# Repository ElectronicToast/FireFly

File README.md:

# FireFly

Open source ATmega8 target board with voltage regulation and ICSP, FTDI breakouts.

&nbsp;

## Description

FIREFLY is an open-source ATmega8 (ATmega328) target board that might be likened to a lightweight yet accessible Arduino Uno R3. It is intended to be used for learning AVR C/C++ or AVR Assembly with Atmel Studio. A 16 MHz oscillator and reset circuit is provided for a complete microcontroller system. 5V and 3V3 power are created from DC input. The 28 pins of the ATmega8 DIP package are brought out onto breadboard-compatible headers so that the whole board may be plugged directly into a breadboard and used.

The ATmega8 may be programmed through the onboard ICSP or FTDI headers with an appropriate programmer. The power source for the target may be selected by a jumper shunt; when programming, take care not to power the target through the DC input (VIN) in addition to the programmer.

Designed with KiCad EDA 5.0.1. Gerber and drill files for fabrication may be found in `/gerber`, while documentation in pdf format may be found in `/pdf`. 

## Author
- Ray Sun - Undergraduate, Electrical Engineering, Caltech, Class of 2020

I created this board to help me enhance my knowledge of embedded systems development and working with AVRs.

## Licensing
<br />This work is licensed under a <a rel="license" href="http://creativecommons.org/licenses/by-sa/3.0/">Creative Commons Attribution-ShareAlike 3.0 Unported License</a>.

This design is a derivative of the [Arduino Uno Rev3](https://store.arduino.cc/usa/arduino-uno-rev3) board and is inspired by Adafruit Industries' [DC Boarduino](https://www.adafruit.com/product/72) by Limor Fried. Arduino is a trademark of Arduino AG. This design is not affiliated with Arduino AG.

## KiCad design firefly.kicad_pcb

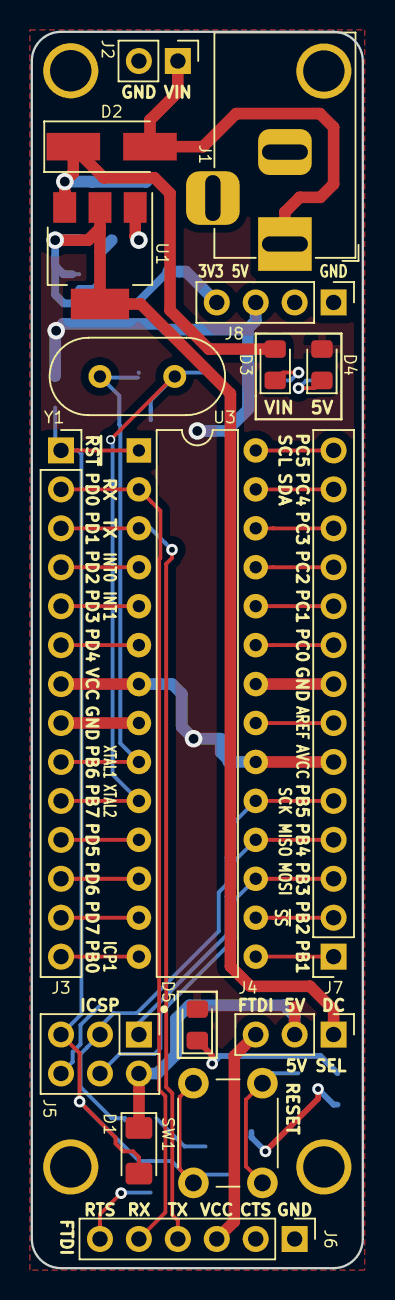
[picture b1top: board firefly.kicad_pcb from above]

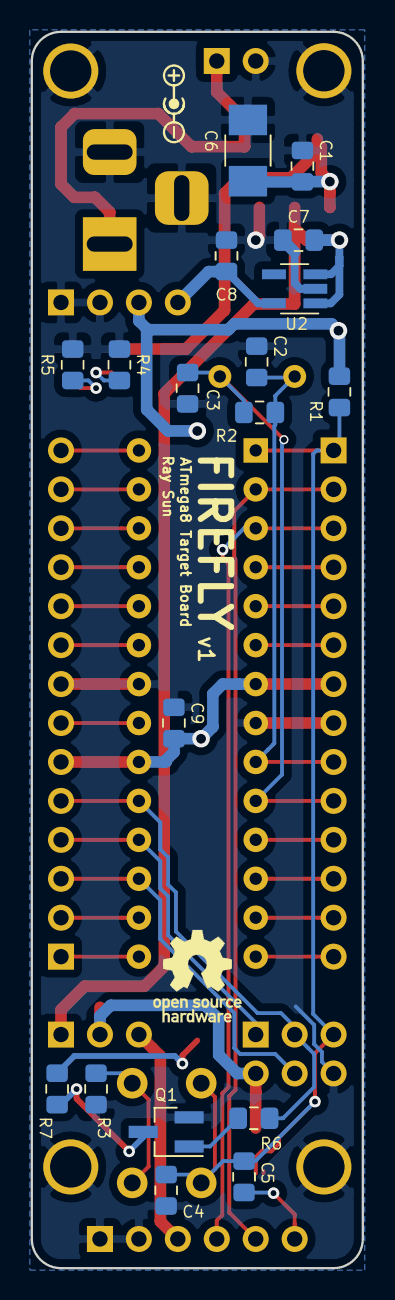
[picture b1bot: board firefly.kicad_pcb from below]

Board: 2 copper layers, 21.6 x 80.6 mm, 35 parts (18 on the bottom side), 38 nets.

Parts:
C1, C7: 10uF; C_0805_2012Metric_Pad1.15x1.40mm_HandSolder
C2, C3: 20pF; C_0805_2012Metric_Pad1.15x1.40mm_HandSolder
C4, C8: 1uF; C_0805_2012Metric_Pad1.15x1.40mm_HandSolder
C5, C9: 0.1uF; C_0805_2012Metric_Pad1.15x1.40mm_HandSolder
C6: 10uF; C_1210_HandSoldering
D1: CD1206-S01575; D_1206_3216Metric_Pad1.42x1.75mm_HandSolder
D2: M7; D_SMA_Handsoldering
D3: LTST-C171KRKT; LED_0805_2012Metric_Pad1.15x1.40mm_HandSolder
D4: LTST-C171KGKT; LED_0805_2012Metric_Pad1.15x1.40mm_HandSolder
D5: LTST-C171TBKT; LED_0805_2012Metric_Pad1.15x1.40mm_HandSolder
J1: Barrel_Jack; BarrelJack_Horizontal
J2: Conn_01x02; PinHeader_1x02_P2.54mm_Vertical
J3, J7: Conn_01x14; PinSocket_1x14_P2.54mm_Vertical
J4: Power_Jumper; PinHeader_1x03_P2.54mm_Vertical
J5: Conn_02x03_Odd_Even; PinHeader_2x03_P2.54mm_Vertical
J6: Conn_01x06; PinHeader_1x06_P2.54mm_Vertical
J8: Conn_01x04; PinHeader_1x04_P2.54mm_Vertical
Q1: NTR5103; SOT-23_Handsoldering
R1: 10K; R_0805_2012Metric_Pad1.15x1.40mm_HandSolder
R2: 1M; R_0805_2012Metric_Pad1.15x1.40mm_HandSolder
R3: 100; R_0805_2012Metric_Pad1.15x1.40mm_HandSolder
R4, R5, R6: 1K; R_0805_2012Metric_Pad1.15x1.40mm_HandSolder
R7: 330; R_0805_2012Metric_Pad1.15x1.40mm_HandSolder
SW1: SW_Push; SW_PUSH_6mm
U1: NCP1117-5.0_SOT223; SOT-223-3_TabPin2
U2: LP2985-3.3; SOT-23-5_HandSoldering
U3: ATmega328P-PU; DIP-28_W7.62mm
Y1: 16 MHz; Crystal_HC49-4H_Vertical

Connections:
+3V3: C8.1, J8.4, U2.5
+5V: C9.1, D1.1, D4.2, D5.2, J3.7, J4.2, J5.2, J7.6, J8.3, R1.1, U3.7, U3.20
/DC_5V: C7.1, J4.1, U1.2, U2.1, U2.3
/MISO: J5.1, J7.4, U3.18
/MOSI: J5.4, J7.3, U3.17
/OSC1: C2.1, J3.9, R2.1, U3.9, Y1.1
/OSC2: C3.1, J3.10, R2.2, U3.10, Y1.2
/P1: C4.1, C5.2, D1.2, J3.1, J5.5, R1.2, SW1.1, U3.1
/P2: J3.2, J6.5, U3.2
/P3: J3.3, J6.4, U3.3
/P4: J3.4, U3.4
/P5: J3.5, U3.5
/P6: J3.6, U3.6
/P11: J3.11, U3.11
/P12: J3.12, U3.12
/P13: J3.13, U3.13
/P14: J3.14, U3.14
/P15: J7.1, U3.15
/P16: J7.2, U3.16
/P19: J5.3, J7.5, R6.2, U3.19
/P21: J7.7, U3.21
/P23: J7.9, U3.23
/P24: J7.10, U3.24
/P25: J7.11, U3.25
/P26: J7.12, U3.26
/P27: J7.13, U3.27
/P28: J7.14, U3.28
/RTS#: C5.1, J6.6
/USB_5V: J4.3, J6.3
/VIN: D2.2, J1.1, J2.1
GND: C1.2, C2.2, C3.2, C4.2, C6.2, C7.2, C8.2, C9.2, J1.2, J1.3, J2.2, J3.8, J5.6, J6.1, J6.2, J7.8, J8.1, J8.2, Q1.2, R3.1, R4.2, R5.2, U1.1, U2.2, U3.8, U3.22
unnamed: D3.1, R4.1
unnamed: D4.1, R5.1
unnamed: D5.1, R7.1
unnamed: Q1.1, R6.1
unnamed: Q1.3, R7.2
unnamed: R3.2, SW1.2
VDD: C1.1, C6.1, D2.1, D3.2, U1.3

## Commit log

2018-09-26 Added files.
2018-09-30 Moved some components and silkscreen around, replaced crystal.
2018-11-10 Add files for v1 release
2018-11-10 Remove old Gerbers and add zip
2018-12-24 Add physical board image
